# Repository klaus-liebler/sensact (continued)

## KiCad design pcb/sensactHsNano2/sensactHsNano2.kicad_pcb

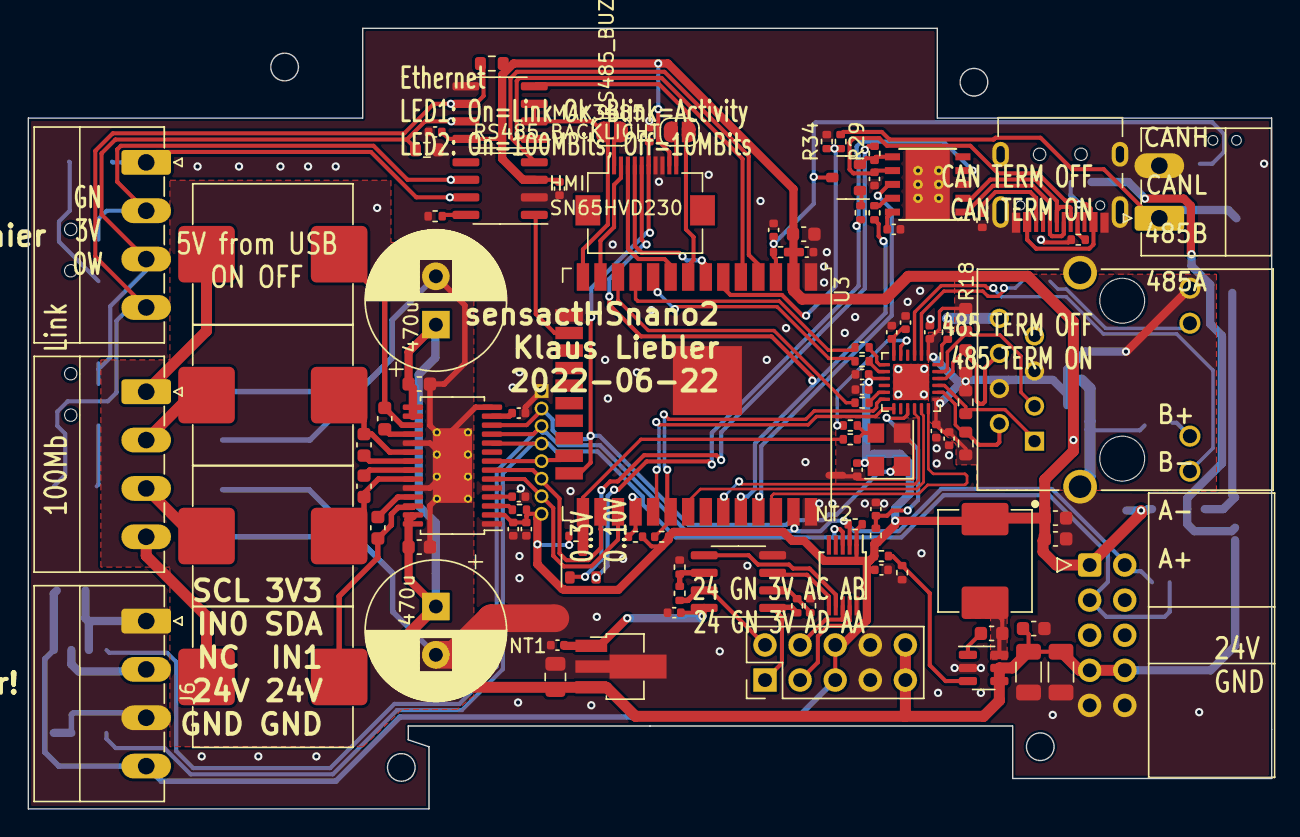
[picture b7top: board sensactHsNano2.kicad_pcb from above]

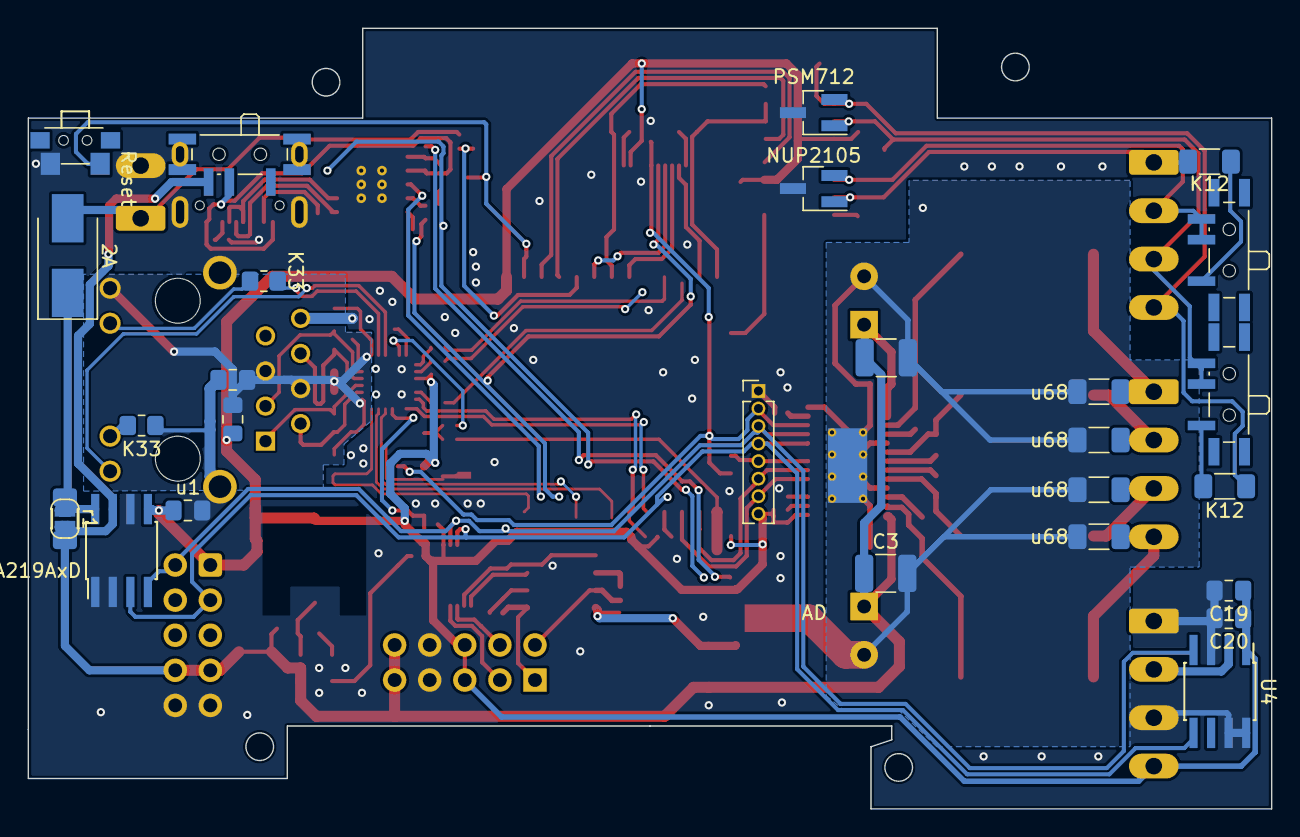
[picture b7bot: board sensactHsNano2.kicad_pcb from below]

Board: 2 copper layers, 90.0 x 56.5 mm, 130 parts (27 on the bottom side), 99 nets.

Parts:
C1, C8: 470u; CP_Radial_D10.0mm_P3.50mm
C2, C26, C29: 4u7; C_0402_1005Metric
C3, C9: 22u; C_1210_3225Metric_Pad1.33x2.70mm_HandSolder
C4, C21, C22, C25, C27, C28, C31, C32, C40, C41, C42, C44, C45, C46, C47: u1; C_0402_1005Metric
C5, C10, C36, C37: u1; C_0603_1608Metric
C6, C7, C24: 1u; C_0402_1005Metric
C11, C12, C13, C14: u22; C_0603_1608Metric
C15, C16, C17, C18: u68; C_1206_3216Metric_Pad1.33x1.80mm_HandSolder
C19: 1u; C_0805_2012Metric_Pad1.18x1.45mm_HandSolder
C20, C48: u1; C_0805_2012Metric_Pad1.18x1.45mm_HandSolder
C23: n47; C_0402_1005Metric
C30: 22n; C_0805_2012Metric_Pad1.18x1.45mm_HandSolder
C33, C38, C39: 22u; C_0603_1608Metric
C34, C35: 10u; C_1206_3216Metric
C43: u47; C_0805_2012Metric
D1: PSM712; SOT-23_Handsoldering
D2: 2A; D_SMB_Handsoldering
D3: NUP2105; SOT-23_Handsoldering
FB1: Bead; L_0805_2012Metric_Pad1.15x1.40mm_HandSolder
J1: HMI; Hirose_FH12-10S-0.5SH_1x10-1MP_P0.50mm_Horizontal
J2: SensactBusConnector; IDC-Header_2x05_P2.54mm_Horizontal_tightCrtYd
J3: CAN+485; PhoenixContact_MC_1,5_4-G-3.5_1x04_P3.50mm_Horizontal
J4: HR911105A; RJ45_HANRUN_HR911105A
J5: Audio; PhoenixContact_MC_1,5_4-G-3.5_1x04_P3.50mm_Horizontal
J6: OneWire; PhoenixContact_MC_1,5_4-G-3.5_1x04_P3.50mm_Horizontal
J7: PROG; USB_C_Receptacle_HRO_TYPE-C-31-M-12_smaller
J8: Conn_01x10; PinHeader_2x05_P2.54mm_Vertical
J9: 24V; PhoenixContact_MC_1,5_2-G-3.81_1x02_P3.81mm_Horizontal
J10: I2S_EXT; PinHeader_1x08_P1.27mm_Vertical
JP1: RS485_BUZZER; SolderJumper-2_P1.3mm_Open_RoundedPad1.0x1.5mm
JP2: RS485_BACKLIGHT; SolderJumper-2_P1.3mm_Open_RoundedPad1.0x1.5mm
JP3: SolderJumper_2_Open; SolderJumper-2_P1.3mm_Open_RoundedPad1.0x1.5mm
L1, L2, L3, L4: 10u; L_1040
L5: 4u7; L_Abracon_ASPI-0630LR
NT1: Net-Tie_2; NetTie-2_SMD_Pad2.0mm
NT2: NetTie_2; NetTie-2_SMD_Pad0.5mm
Q1, Q2: BC817; SOT-23_smaller
R1, R3, R4, R6, R33, R47: 4k7; R_0402_1005Metric
R2: r1; R_1206_3216Metric_Pad1.30x1.75mm_HandSolder
R5: 1K5; R_0402_1005Metric
R7, R23: K12; R_1206_3216Metric_Pad1.30x1.75mm_HandSolder
R8, R9, R10, R12, R14: 33R; R_0402_1005Metric
R11, R28, R34: 1k; R_0402_1005Metric
R13, R22: 1k; R_0603_1608Metric
R15, R17, R18, R19: 49R9; R_0603_1608Metric
R16: 12K1; R_0402_1005Metric
R20, R21: K33; R_0805_2012Metric_Pad1.20x1.40mm_HandSolder
R24: 47k; R_0402_1005Metric
R25, R29, R31, R32, R41, R48: 10k; R_0402_1005Metric
R26: 15k; R_0402_1005Metric
R27, R30: 5k1; R_0402_1005Metric
R51, R52: 22k; R_0402_1005Metric
SW1: TERM ON; SW_SPDT_PCM12_handsolder
SW2: OFF TERM ON; SW_SPDT_PCM12_handsolder
SW3: Reset; Button_2x4x3,5_handsolder
SW4: PROG_PWR; SW_SPDT_PCM12_handsolder
U1: TAS5805M; HTSSOP-28-1EP_4.4x9.7mm_P0.65mm_EP2.85x5.4mm_ThermalVias
U2: LAN8720A; QFN-24-1EP_4x4mm_P0.5mm_EP2.6x2.6mm
U3: ESP32; ESP32-WROOM-32U
U4: DS2482; SOIC-8_3.9x4.9mm_Pitch1.27mm_handsolder
U5: SN65HVD230; SOIC-8_3.9x4.9mm_P1.27mm
U6: MAX3485; SOIC-8_3.9x4.9mm_P1.27mm
U7: RY8310; SOT-23-6
U8: LM358; SOIC-8_3.9x4.9mm_P1.27mm
U9: MCP4728; MSOP-10_3x3mm_P0.5mm
U10: INA219AxD; SOIC-8_3.9x4.9mm_Pitch1.27mm_handsolder
U11: L78L15_SOT89; SOT-89-3_Handsoldering
U12: CH340K; SSOP-10_3.9x4.9mm_P1.00mm_EP
X1: 50MHz; Oscillator_SMD_SeikoEpson_SG8002CE-4Pin_3.2x2.5mm

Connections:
485_DE: JP1.1 (A), U3.14 (IO12), U6.2 (~RE), U6.3 (DE)
485_DI: JP2.1 (A), U3.8 (IO32), U6.4 (DI)
485_RO: U3.5 (SENSOR_VN), U6.1 (RO)
+3V3: C2.1, C4.1, C19.1, C20.1, C21.1, C22.1, C25.1, C26.1, C31.2, C32.1, C33.1, C38.1, C39.1, C47.2, C48.2, FB1.2, J1.9, J2.1 (3V3), J6.4, J8.5, J8.6, J10.8, L5.1, R1.1, R4.1, R5.2, R6.1, R11.1, R22.1, R24.1, R25.1, R47.1, U1.2 (DVDD), U2.9 (VDDIO), U3.2 (VDD), U4.1 (VCC), U5.3 (VCC), U6.8 (VCC), U9.1 (VDD), U10.5 (VS), X1.4 (V+)
+5P: C42.2, J7.A4 (VBUS), J7.A9 (VBUS), J7.B4 (VBUS), J7.B9 (VBUS), SW4.2 (B), U12.7 (VCC)
+15V: C44.2, C46.2, U8.8 (V+), U11.1 (OUT)
+24V: C1.1, C3.1, C5.1, C8.1, C9.1, C10.1, C34.2, C35.2, C36.2, C43.1, J2.7 (24V), J2.8 (24V), J8.9, J8.10, JP3.2 (B), R2.2, SW4.3 (C), U1.15 (PVDD), U1.16 (PVDD), U1.27 (PVDD), U1.28 (PVDD), U7.4 (~SHDN), U7.5 (VIN), U10.7 (IN-), U11.3 (IN)
/AO0: J8.1, R52.1, U8.1
/AO1: J8.2, R51.1, U8.7
/VOUTA: U8.3 (+), U9.6 (VOUTA)
/VOUTB: U8.5 (+), U9.7 (VOUTB)
/VOUTC: J8.4, U9.8 (VOUTC)
/VOUTD: J8.3, U9.9 (VOUTD)
/audioamplifier/ADR: R4.2, U1.3 (ADR/FAULT)
/audioamplifier/AVDD: C6.1, U1.13 (AVDD)
/audioamplifier/VR_DIG: C7.1, U1.4 (VR_DIG)
/eth/CLK_GND: C21.2, NT2.1, X1.2 (GND)
/eth/CRS: R12.2, U2.11 (CRS_DV/MODE2)
/eth/LED1: J4.9, U2.3 (LED1/REGOFF)
/eth/LED2: R20.2, U2.2 (LED2/nINTSEL)
/eth/RBIAS: R16.2, U2.24 (RBIAS)
/eth/RST: C45.1, R47.2, U2.15 (RST)
/eth/RX0: R9.1, U2.8 (RXD0/MODE0)
/eth/RX1: R10.2, U2.7 (RXD1/MODE1)
/eth/RX_N: J4.6, R19.2, U2.22 (RXN)
/eth/RX_P: J4.3, R18.2, U2.23 (RXP)
/eth/TX_N: J4.2, R17.2, U2.20 (TXN)
/eth/TX_P: J4.1, R15.2, U2.21 (TXP)
/eth/VDDA: C27.1, C28.1, C29.1, C30.1, FB1.1, J4.4, J4.5, J4.12, R15.1, R17.1, R18.1, R19.1, U2.1 (VDD2A), U2.19 (VDD1A)
/eth/VDDCR: C23.1, C24.1, U2.6 (VDDCR)
/prog/DTR: Q1.2 (E), R32.2, U12.4 (DTR)
/prog/RTS: Q2.2 (E), R31.2, U12.6 (RTS)
/prog/UD+: J7.A6 (D+), J7.B6 (D+), U12.1 (UD+)
/prog/UD-: J7.A7 (D-), J7.B7 (D-), U12.2 (UD-)
/psu/SW: C37.2, L5.2, U7.6 (SW)
AMP_PDN: J1.6, J10.2, R33.1, U1.12 (PDN), U3.24 (IO2), X1.1 (EN)
BACKLIGHT: J1.10, JP2.2 (B)
BUZZER: J1.1, JP1.2 (B)
CANH: D3.1 (A1), J3.1, R7.2, U5.7 (CANH)
CANL: D3.2 (A2), J3.2, SW1.2 (B), SW1.3 (C), U5.6 (CANL)
CAN_RX: U3.4 (SENSOR_VP), U5.4 (R)
CAN_TX: U3.16 (IO13), U5.1 (D)
ETH_CLK: Q1.3 (C), R8.1, R25.2, U3.25 (IO0)
ETH_CRS: R12.1, U3.12 (IO27)
ETH_MDC: U2.13 (MDC), U3.29 (IO5)
ETH_MDIO: R5.1, U2.12 (MDIO), U3.30 (IO18)
ETH_RX0: R9.2, U3.10 (IO25)
ETH_RX1: R10.1, U3.11 (IO26)
ETH_TX0: U2.17 (TXD0), U3.31 (IO19)
ETH_TX1: U2.18 (TXD1), U3.36 (IO22)
ETH_TXEN: U2.16 (TXEN), U3.33 (IO21)
GND: C2.2, C4.2, C6.2, C7.2, C19.2, C20.2, C22.2, C23.2, C24.2, C25.2, C26.2, C27.2, C28.2, C29.2, C30.2, C31.1, C32.2, C33.2, C34.1, C35.1, C36.1, C38.2, C39.2, C40.2, C41.2, C42.1, C43.2, C44.1, C45.2, C46.1, C47.1, C48.1, D1.3 (A), D3.3 (common), J1.7, J1.8, J2.9 (GND), J2.10 (GND), J4.8, J4.15 (SHIELD), J4.16 (SHIELD), J6.1, J6.3, J7.A1 (GND), J7.A12 (GND), J7.B1 (GND), J7.B12 (GND), J7.S1 (SHIELD), J8.7, J8.8, J9.2, J10.1, NT1.1, NT2.2, R3.2, R13.2, R16.1, R21.1, R26.1, R27.1, R30.1, R33.2, R34.2, R41.2, R48.2, SW3.1, U1.1 (DGND), U1.5 (DGND), U2.25 (VSS), U3.1 (GND), U3.15 (GND), U3.38 (GND), U3.39 (GND), U4.3 (GND), U4.7 (AD1), U4.8 (AD0), U5.2 (GND), U6.5 (GND), U7.2 (GND), U8.4 (V-), U9.10 (VSS), U10.1 (A1), U10.2 (A0), U10.6 (GND), U11.2 (GND), U12.3 (GND), U12.11 (PAD_GND)
GNDA: C1.2, C3.2, C5.2, C8.2, C9.2, C10.2, C15.1, C16.1, C17.1, C18.1, NT1.2, U1.14 (AGND), U1.19 (PGND), U1.24 (PGND), U1.29 (PAD)
I2S_LRCLK: J10.7, U1.6 (LRCLK), U3.27 (IO16)
I2S_SCLK: J10.6, U1.7 (SCLK), U3.26 (IO4)
I2S_SDAT: J10.5, U1.8 (SDIN), U3.23 (IO15)
MOSI: J1.2, U3.13 (IO14)
unnamed: C11.1, L1.2, U1.26 (OUT_A+)
unnamed: C11.2, U1.25 (BST_A+)
unnamed: C12.1, L2.2, U1.23 (OUT_A-)
unnamed: C12.2, U1.22 (BST_A-)
unnamed: C13.1, L3.2, U1.17 (OUT_B+)
unnamed: C13.2, U1.18 (BST_B+)
unnamed: C14.1, L4.2, U1.20 (OUT_B-)
unnamed: C14.2, U1.21 (BST_B-)
unnamed: C37.1, U7.1 (CB)
unnamed: D2.1 (K), JP3.1 (A), R2.1, U10.8 (IN+)
unnamed: D2.2 (A), J9.1, R29.1
unnamed: J4.10, R21.2
unnamed: J4.11, R20.1
unnamed: Q1.1 (B), R31.1
unnamed: Q2.1 (B), R32.1
unnamed: R3.1, U5.8 (Rs)
unnamed: R7.1, SW1.1 (A)
unnamed: R8.2, R14.1, X1.3 (OUT)
unnamed: R14.2, U2.5 (XTAL1/CLKIN)
unnamed: R23.2, SW2.1 (A)
unnamed: R24.2, R26.2, U7.3 (FB)
unnamed: J7.A5 (CC1), R27.2
unnamed: J7.B5 (CC2), R30.2
unnamed: R41.1, R51.2, U8.6 (-)
unnamed: R48.1, R52.2, U8.2 (-)
unnamed: C41.1, U12.10 (V3)
OUT_A+: C17.2, J5.4, L1.1
OUT_A-: C15.2, J5.3, L2.1
OUT_B+: C18.2, J5.1, L3.1
OUT_B-: C16.2, J5.2, L4.1
OneWire: J6.2, U4.2 (IO)
PROG_EN: C40.1, Q2.3 (C), R11.2, SW3.2, U3.3 (EN)
PROG_RX: R28.1, U12.9 (RXD)
PROG_TX: U3.35 (TXD0/IO1), U12.8 (TXD)
RS: J1.5, R28.2, U3.34 (RXD0/IO3)
RS485A: D1.2 (K), J3.4, R22.2, R23.1, U6.6 (A)
RS485B: D1.1 (K), J3.3, R13.1, SW2.2 (B), SW2.3 (C), U6.7 (B)
SCL1: J2.2 (SCL), J10.3, R6.2, U1.11 (SCL), U3.37 (IO23), U4.4 (SCL), U9.2 (SCL), U10.4 (SCL)
SCLK: J1.3, U3.9 (IO33)
SDA1: J2.3 (SDA), J10.4, R1.2, U1.10 (SDA), U3.28 (IO17), U4.5 (SDA), U9.3 (SDA), U10.3 (SDA)
SUPPLY_MONITOR: R29.2, R34.1, U3.6 (IO34)
SW1: J1.4, U3.7 (IO35)
